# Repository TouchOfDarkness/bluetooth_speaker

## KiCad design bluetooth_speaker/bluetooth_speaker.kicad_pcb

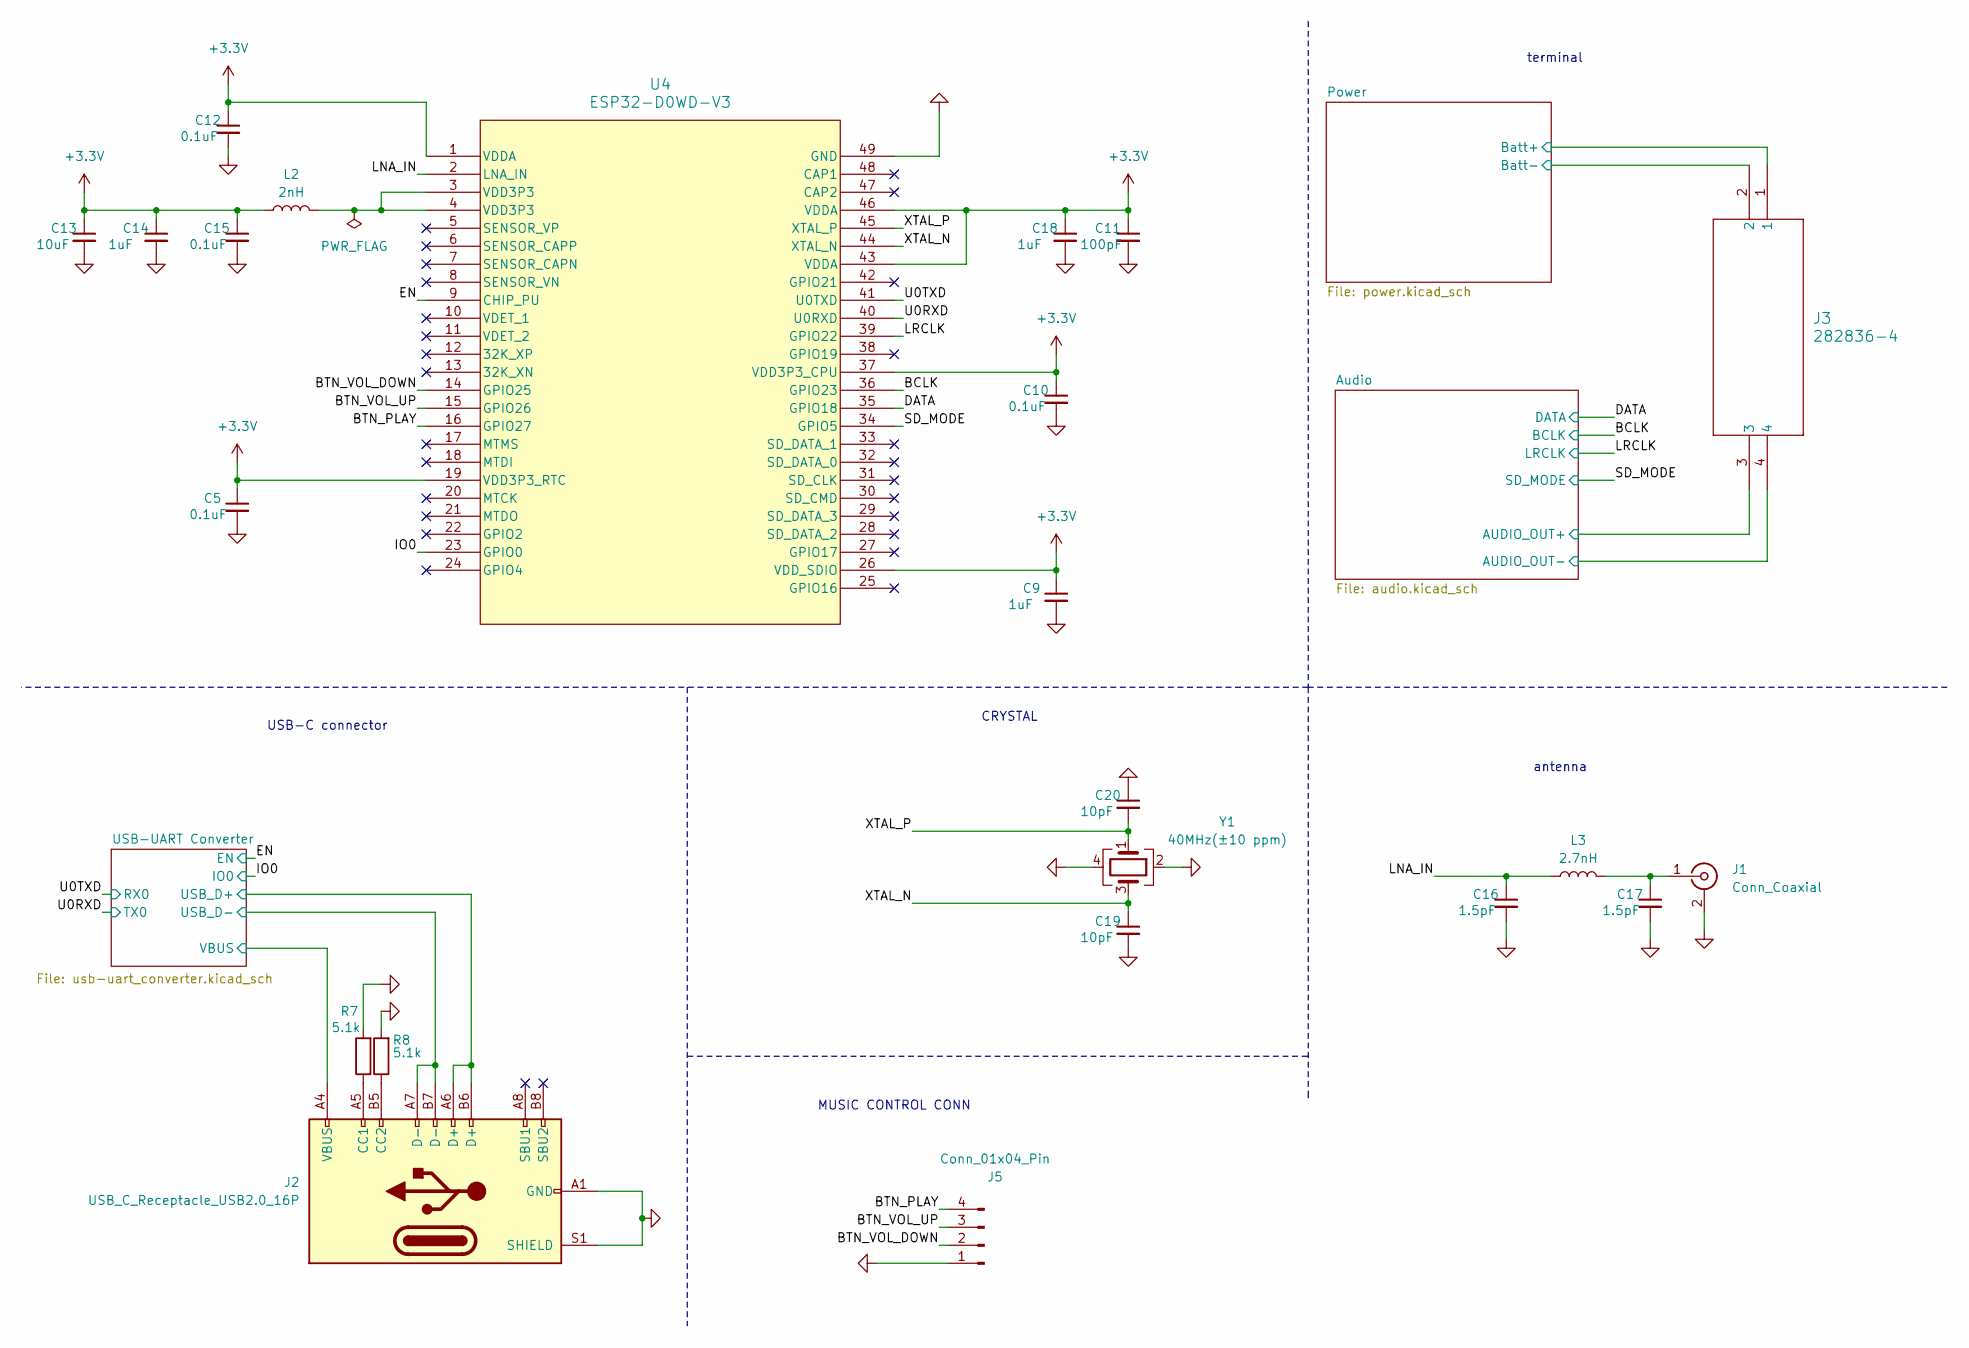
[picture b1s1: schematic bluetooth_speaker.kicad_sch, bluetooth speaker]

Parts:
C5, C10, C12, C15: 0.1uF; C_0603_1608Metric_Pad1.08x0.95mm_HandSolder
C9, C14, C18: 1uF; C_0603_1608Metric_Pad1.08x0.95mm_HandSolder
C11: 100pF; C_0603_1608Metric_Pad1.08x0.95mm_HandSolder
C13: 10uF; C_0603_1608Metric_Pad1.08x0.95mm_HandSolder
C16, C17: 1.5pF; CAPC3216X94N
C19, C20: 10pF; C_0603_1608Metric_Pad1.08x0.95mm_HandSolder
J1: Conn_Coaxial; SMA_Samtec_SMA-J-P-H-ST-EM1_EdgeMount
J2: USB_C_Receptacle_USB2.0_16P; USB_C_Receptacle_GCT_USB4085
J3: 282836-4; 282836-4_TYC
J5: Conn_01x04_Pin; JST_PH_B4B-PH-K_1x04_P2.00mm_Vertical
L2: 2nH; MHQ1005
L3: 2.7nH; LQW2BAN11NG00L
R7, R8: 5.1k; R_0603_1608Metric_Pad0.98x0.95mm_HandSolder
U4: ESP32-D0WD-V3; QFN48_ESP32-D0WD-V3_EXP
Y1: 40MHz(±10 ppm); FW400WFMR1

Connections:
+3.3V: C5.1, C9.1, C10.1, C11.1, C12.1, C13.1, C14.1, C15.1, C18.1, L2.1, U4.1 (VDDA), U4.19 (VDD3P3_RTC), U4.26 (VDD_SDIO), U4.37 (VDD3P3_CPU), U4.43 (VDDA), U4.46 (VDDA); also elsewhere on the board
/Audio/AUDIO_OUT+: J3.3; also elsewhere on the board
/Audio/AUDIO_OUT-: J3.4; also elsewhere on the board
/BCLK: U4.36 (GPIO23); also elsewhere on the board
/BTN_PLAY: J5.4, U4.16 (GPIO27)
/BTN_VOL_DOWN: J5.2, U4.14 (GPIO25)
/BTN_VOL_UP: J5.3, U4.15 (GPIO26)
/DATA: U4.35 (GPIO18); also elsewhere on the board
/EN: U4.9 (CHIP_PU); also elsewhere on the board
/IO0: U4.23 (GPIO0); also elsewhere on the board
/LNA_IN: C16.1, L3.1, U4.2 (LNA_IN)
/LRCLK: U4.39 (GPIO22); also elsewhere on the board
/Power/Batt+: J3.1; also elsewhere on the board
/SD_MODE: U4.34 (GPIO5); also elsewhere on the board
/U0RXD: U4.40 (U0RXD); also elsewhere on the board
/U0TXD: U4.41 (U0TXD); also elsewhere on the board
/USB-UART Converter/USB_D+: J2.A6 (D+), J2.B6 (D+); also elsewhere on the board
/USB-UART Converter/USB_D-: J2.A7 (D-), J2.B7 (D-); also elsewhere on the board
/USB-UART Converter/VBUS: J2.A4 (VBUS), J2.A9 (VBUS), J2.B4 (VBUS), J2.B9 (VBUS); also elsewhere on the board
/XTAL_N: C19.1, U4.44 (XTAL_N), Y1.3
/XTAL_P: C20.2, U4.45 (XTAL_P), Y1.1
GND: C5.2, C9.2, C10.2, C11.2, C12.2, C13.2, C14.2, C15.2, C16.2, C17.2, C18.2, C19.2, C20.1, J1.2 (Ext), J2.A1 (GND), J2.A12 (GND), J2.B1 (GND), J2.B12 (GND), J2.S1 (SHIELD), J3.2, J5.1, R7.2, R8.2, U4.49 (GND), Y1.2, Y1.4; also elsewhere on the board
unnamed: C17.1, J1.1 (In), L3.2
unnamed: J2.A5 (CC1), R7.1
unnamed: J2.B5 (CC2), R8.1
unnamed: L2.2, U4.3 (VDD3P3), U4.4 (VDD3P3)

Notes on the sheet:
CRYSTAL
antenna
USB-C connector
terminal
MUSIC CONTROL CONN

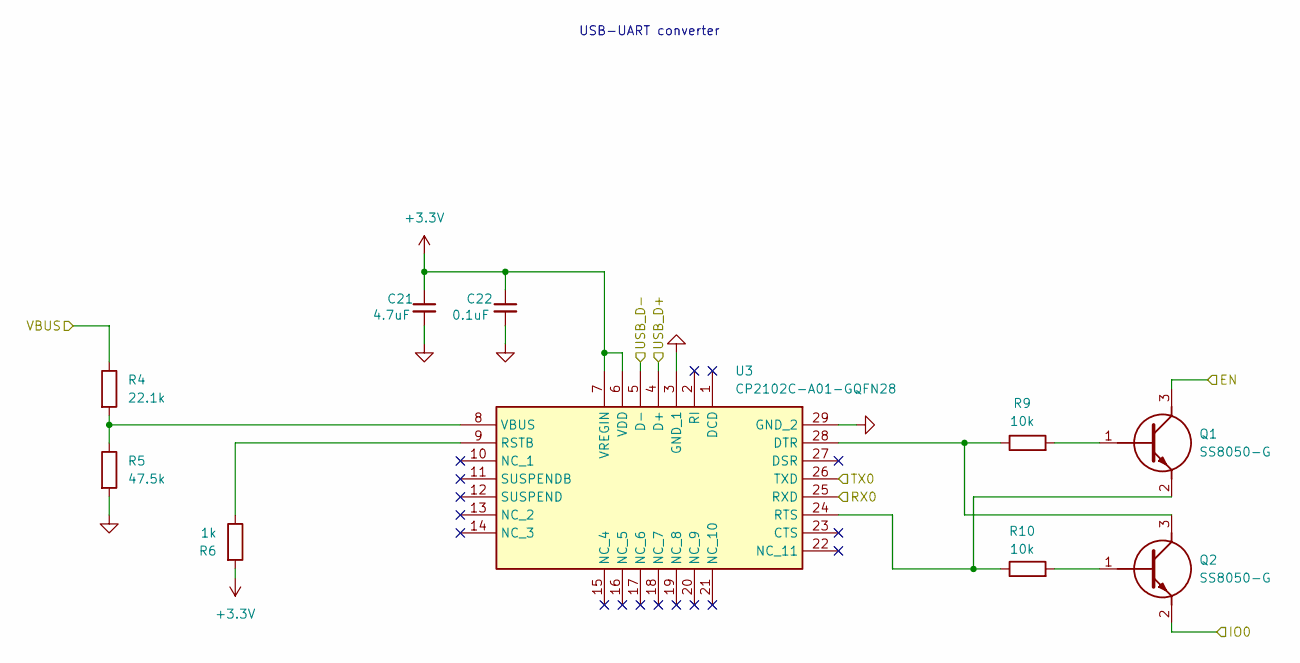
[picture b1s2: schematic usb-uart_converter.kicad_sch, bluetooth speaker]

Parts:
C21: 4.7uF; C_0603_1608Metric_Pad1.08x0.95mm_HandSolder
C22: 0.1uF; C_0603_1608Metric_Pad1.08x0.95mm_HandSolder
Q1, Q2: SS8050-G; SOT95P240X115-3N; Mouser Part Number 750-SS8050-G
R4: 22.1k; R_0603_1608Metric_Pad0.98x0.95mm_HandSolder
R5: 47.5k; R_0603_1608Metric_Pad0.98x0.95mm_HandSolder
R6: 1k; R_0603_1608Metric_Pad0.98x0.95mm_HandSolder
R9, R10: 10k; R_0603_1608Metric_Pad0.98x0.95mm_HandSolder
U3: CP2102C-A01-GQFN28; QFN50P500X500X80-29N-D; Mouser Part Number 634-P2102CA01GQFN28

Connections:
+3.3V: C21.1, C22.1, R6.2, U3.6 (VDD), U3.7 (VREGIN); also elsewhere on the board
/EN: Q1.3 (C); also elsewhere on the board
/IO0: Q2.2 (E); also elsewhere on the board
/U0RXD: U3.26 (TXD); also elsewhere on the board
/U0TXD: U3.25 (RXD); also elsewhere on the board
/USB-UART Converter/USB_D+: U3.4 (D+); also elsewhere on the board
/USB-UART Converter/USB_D-: U3.5 (D-); also elsewhere on the board
/USB-UART Converter/VBUS: R4.1; also elsewhere on the board
GND: C21.2, C22.2, R5.2, U3.3 (GND_1), U3.29 (GND_2); also elsewhere on the board
unnamed: Q1.1 (B), R9.2
unnamed: Q1.2 (E), R10.1, U3.24 (RTS)
unnamed: Q2.1 (B), R10.2
unnamed: Q2.3 (C), R9.1, U3.28 (DTR)
unnamed: R6.1, U3.9 (RSTB)
unnamed: R4.2, R5.1, U3.8 (VBUS)

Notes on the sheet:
USB-UART converter

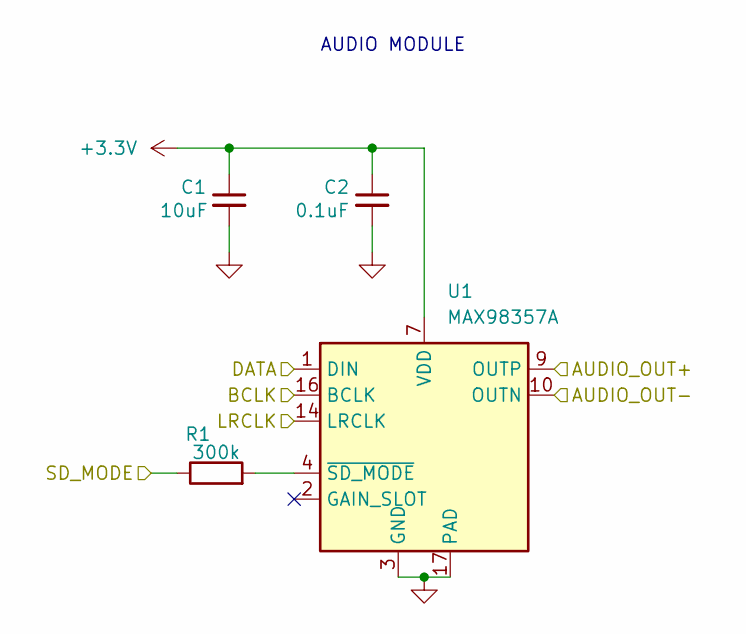
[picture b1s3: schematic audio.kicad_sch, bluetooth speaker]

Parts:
C1: 10uF; C_0603_1608Metric_Pad1.08x0.95mm_HandSolder
C2: 0.1uF; C_0603_1608Metric_Pad1.08x0.95mm_HandSolder
R1: 300k; R_0603_1608Metric_Pad0.98x0.95mm_HandSolder
U1: MAX98357A; TQFN-16-1EP_3x3mm_P0.5mm_EP1.23x1.23mm

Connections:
+3.3V: C1.1, C2.1, U1.7 (VDD), U1.8 (VDD); also elsewhere on the board
/Audio/AUDIO_OUT+: U1.9 (OUTP); also elsewhere on the board
/Audio/AUDIO_OUT-: U1.10 (OUTN); also elsewhere on the board
/BCLK: U1.16 (BCLK); also elsewhere on the board
/DATA: U1.1 (DIN); also elsewhere on the board
/LRCLK: U1.14 (LRCLK); also elsewhere on the board
/SD_MODE: R1.1; also elsewhere on the board
GND: C1.2, C2.2, U1.3 (GND), U1.11 (GND), U1.15 (GND), U1.17 (PAD); also elsewhere on the board
unnamed: R1.2, U1.4 (~SD_MODE)

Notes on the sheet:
AUDIO MODULE

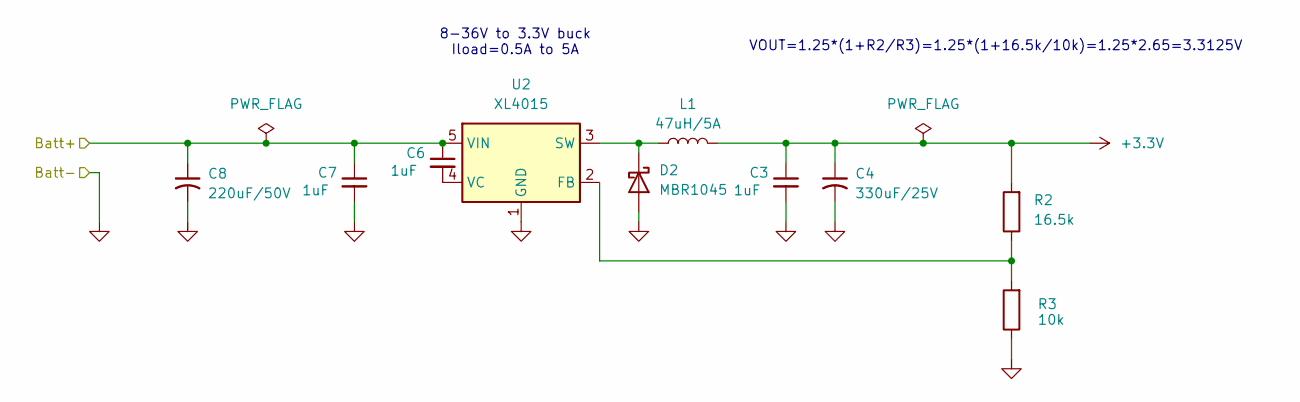
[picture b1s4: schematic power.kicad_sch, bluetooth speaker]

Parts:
C3, C6, C7: 1uF; C_0603_1608Metric_Pad1.08x0.95mm_HandSolder
C4: 330uF/25V; CAPAE1050X1250N
C8: 220uF/50V; CAPAE1050X1250N
D2: MBR1045; TO-220-2_Vertical
L1: 47uH/5A; IHLP5050FDER470M5A
R2: 16.5k; R_0603_1608Metric_Pad0.98x0.95mm_HandSolder
R3: 10k; R_0603_1608Metric_Pad0.98x0.95mm_HandSolder
U2: XL4015; TO-263-5_TabPin3

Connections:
+3.3V: C3.1, C4.1, L1.2, R2.2; also elsewhere on the board
/Power/Batt+: C6.1, C7.1, C8.1, U2.5 (VIN); also elsewhere on the board
GND: C3.2, C4.2, C7.2, C8.2, D2.2 (A), R3.1, U2.1 (GND); also elsewhere on the board
unnamed: D2.1 (K), L1.1, U2.3 (SW)
unnamed: R2.1, R3.2, U2.2 (FB)
unnamed: C6.2, U2.4 (VC)

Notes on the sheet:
VOUT=1.25*(1+R2/R3)=1.25*(1+16.5k/10k)=1.25*2.65=3.3125V
8-36V to 3.3V buck Iload=0.5A to 5A

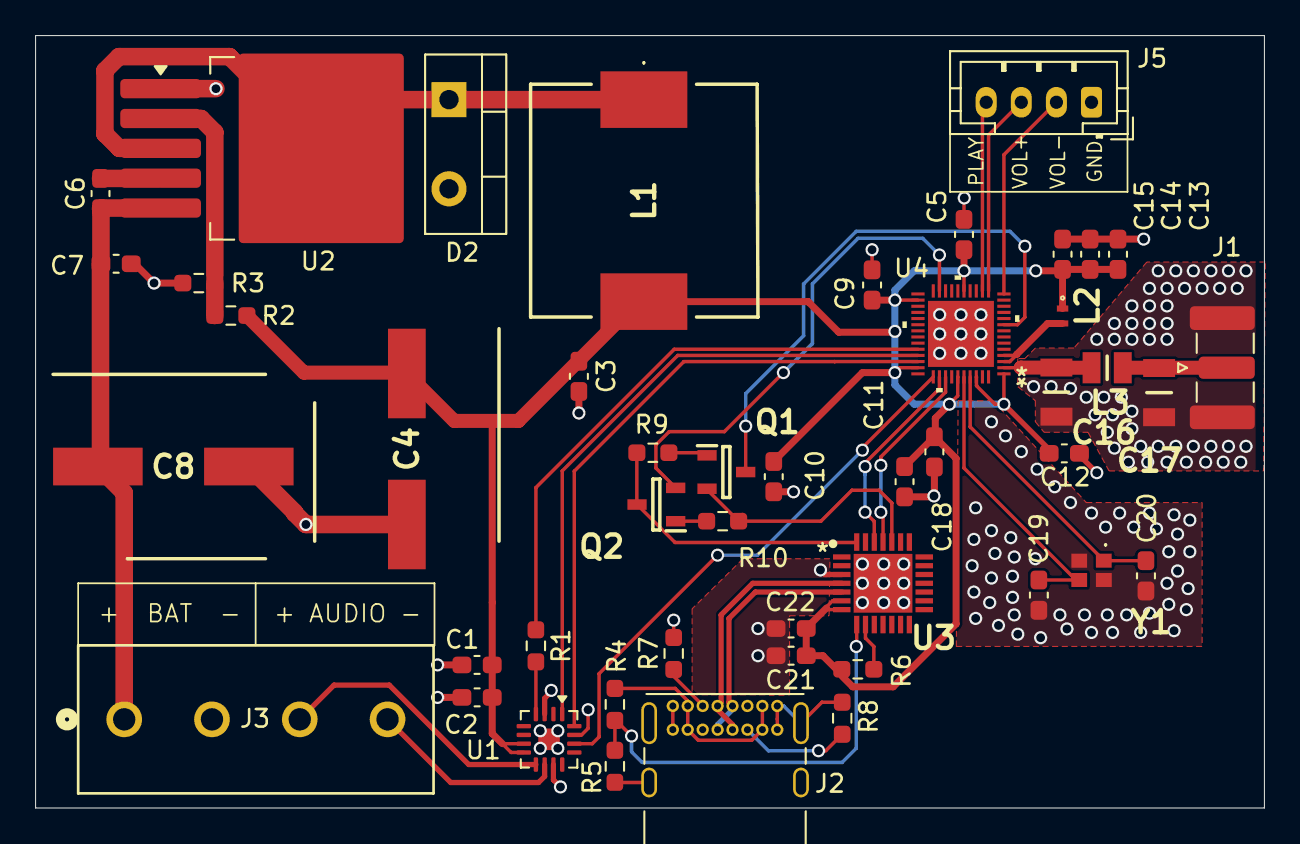
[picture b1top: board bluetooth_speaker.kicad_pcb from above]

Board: 2 copper layers, 70.0 x 44.0 mm, 47 parts (0 on the bottom side), 36 nets.

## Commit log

2025-11-23 repair repository
2025-11-24 Updated files to work on
2025-11-30 Refactor
2025-11-30 Updated schematic
2025-12-01 adding few footprints
2025-12-07 Completed adding footprints, set up PCB rules
2025-12-07 Added missing inductor
2025-12-08 pcb layout
2025-12-14 Realigned components on PCB
2025-12-15 Added auto-programming through CP2102
2025-12-15 lab changes
2025-12-15 again
2025-12-22 Updated PCB traces
2026-01-05 Completed the PCB design
2026-01-05 Exchanged CP2102N to CP2102C due to discontinuation
2026-01-06 Updated crystal design
2026-01-06 added .zip with complete project
